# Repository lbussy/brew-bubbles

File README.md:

---
*It beats watching the grass grow!*

I just did a Google search:

That seems to be pretty important to many homebrewers. Nobody agrees what's "right," and about all the Internet can do is help you pass the time in between trips to stare at the airlock.

Wouldn't it be great if someone made something to tell you when your airlock is bubbling? At the very least, it would cut down on your significant other asking you where you are going at 2:00 AM as you tiptoe out of the bedroom by the light of your cellphone. I mean, we're in a day and age where you can ask your television questions. You'd think someone would make something that could help. What if you don't have computers connected to your grain bin and antennas on your growlers?

Enter Brew Bubbles.

Brew Bubbles will happily count every bubble and report it to you on a web page served by its own web server. Not enough? Brew Bubbles optionally allows you to hook in a couple of very inexpensive and standard temperature probes to display the fermenter and room temperature.

Still not enough, you say?

Well, if you want to go crazy, you can connect Brew Bubbles to [Brewer's Friend](https://www.brewersfriend.com/) and integrate the readings with your recipe journal and see how it all graphs out. Already wired at home? Connect Brew Bubbles into [BrewPi Remix](https://www.brewpiremix.com) or [Fermentrack](https://www.fermentrack.com) and amaze your friends!

Have I piqued your interest? Want to know how to get started? I'm glad you asked. The average garage handyman can build brew Bubbles for around $10, and it takes all of an hour before you are up and running.

Start with the [full documentation](https://brew-bubbles.readthedocs.io/en/latest/), or explore the repository here.

Brew Bubbles is a mature, stable product with no intended roadmap changes. It is maintained for historical reference only. No new releases, upgrades, or individual support are promised. Ask questions in [GitHub Discussions](https://github.com/lbussy/brew-bubbles/discussions) and report reproducible defects in [GitHub Issues](https://github.com/lbussy/brew-bubbles/issues). The original [HomeBrewTalk thread](https://homebrewtalk.com/threads/brew-bubbles-web-enabled-airlock.673559/) remains available as a historical community resource.

I really hope some of you will get some use out of this.

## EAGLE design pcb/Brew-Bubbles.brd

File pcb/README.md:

# 

# Brew Bubbles Shield

This folder contains the Eagle files for printed circuit boards supporting [Brew Bubbles](https://github.com/lbussy/brew-bubbles/).

The shield provides the necessary component connections and circuitry for the ESP-8266 controller used in this project.  It is nearly identical in size to the Wemos D1 mini we use to provide a very compact and lightweight footprint.

[Order from OSHPark.com](https://oshpark.com/shared_projects/NNPU5x7b):

- 2 layer board of 1.01 x 1.13 inches (25.6 x 28.7 mm) 
- $5.65 per set of 3

Please see [the documentation](https://brew-bubbles.readthedocs.io/en/latest/) for additional information.

## BOM

- 3 x C1 0.1μF Ceramic Capacitor (C1-3)
- *2 x 2.2kΩ 1/4W 5% Axial Resistors (R1-2)
- 1 x 150Ω 1/4W 5% Axial Resistor (R3)
- 1 x Sharp GP1A57HR Transmissive Photointerrupter (U1)
- *2 x 3-pin 90° Male Header (ROOM, VESSEL)

This section of the BOM is available on Mouser via [this link](https://www.mouser.com/ProjectManager/ProjectDetail.aspx?AccessID=216fcbe935).

Additionally you will need:

- 1 x Wemos D1 Mini (U2)
- 2 x 8-Pin stacking male headers (almost always comes with the D1)
- 2 x 8-Pin stacking female headers (almost always comes with the D1)
- *2 x Waterproof DS18B20 Temperature Sensor with lead

(*) - Optional items for use when temperature sensors are desired.  They are in the design to provide a means to monitor and trend one's ambient temperature where the fermenter is placed, and/or the fermenting liquid's temperature via a thermowell or insulated in contact with the fermenter. If one chooses not to use these, the firmware will automatically skip reporting these readings.

## 3D-Printed Bracket

See [this project on Thingiverse](https://www.thingiverse.com/thing:4020905) from @gromitdj on [Homebrewtalk.com](https://homebrewtalk.com) (original from @matridium on [Homebrewtalk.com](https://homebrewtalk.com)) for a bracket you can print.

## Modifying These Files
If you would like to personalize these board designs, you may modify them with [Autodesk has removed Eagle as a supported product, the PCBs have not been converted to KiCad].  

The program supports Windows, Linux, and Mac OS X.  EAGLE is available in a [free version](https://www.autodesk.com/products/eagle/free-download), as well as a [subscription-based version with more features](https://www.autodesk.com/products/eagle/compare).

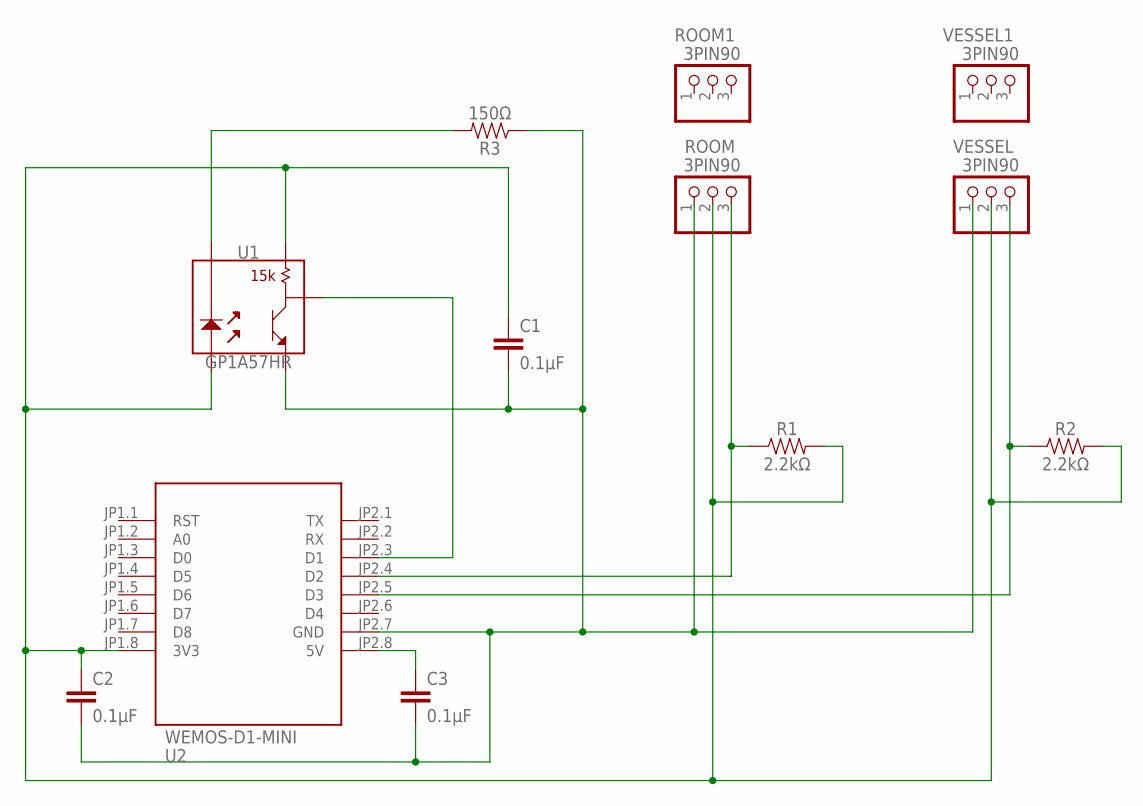
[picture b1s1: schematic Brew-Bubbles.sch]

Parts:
C1, C2, C3: 0.1μF; C025-024X044
R1, R2: 2.2kΩ; AXIAL-0.3
R3: 150Ω; AXIAL-0.3
ROOM, ROOM1: 3PIN90; 1X03/90
U1: GP1A57HR
U2: WEMOS-D1-MINI; WEMOS-D1-MINI-SHIELD
VESSEL, VESSEL1: 3PIN90; 1X03/90

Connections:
3V3: C1.1, C2.1, R1.P$2 (2), R2.P$2 (2), ROOM.2, U1.1, U1.3, U2.JP1.8 (3V3), VESSEL.2
5V: C3.1, U2.JP2.8 (5V)
D1: U1.4, U2.JP2.3 (D1)
D2: R1.P$1 (1), ROOM.3, U2.JP2.4 (D2)
D3: R2.P$1 (1), U2.JP2.5 (D3), VESSEL.3
GND: C1.2, C2.2, C3.2, R3.P$1 (1), ROOM.1, U1.5, U2.JP2.7 (GND), VESSEL.1
PD1: R3.P$2 (2), U1.2

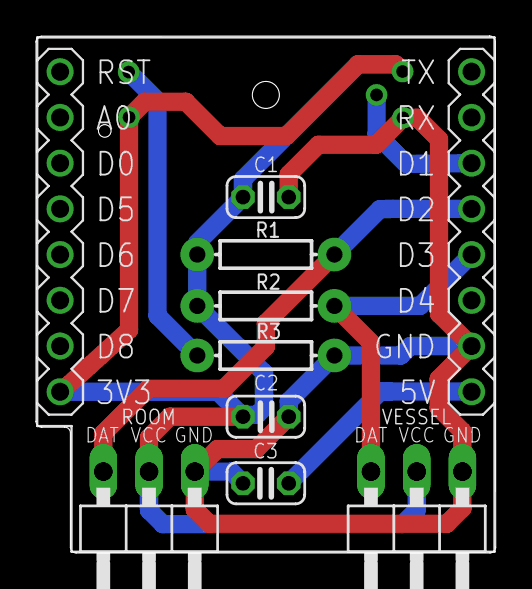
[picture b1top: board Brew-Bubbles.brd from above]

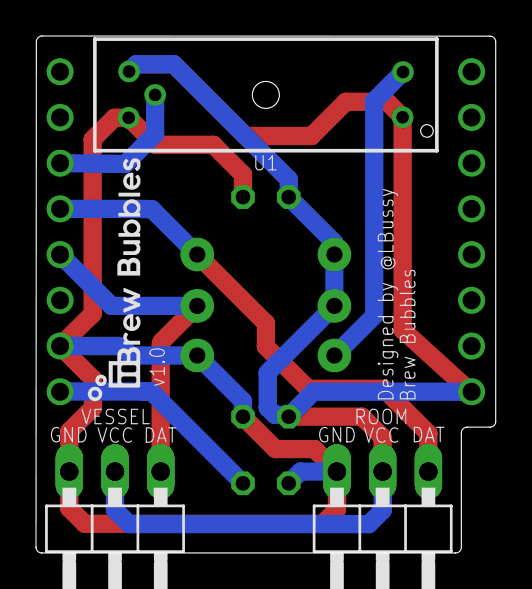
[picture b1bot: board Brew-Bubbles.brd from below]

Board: 2 copper layers, 25.5 x 28.7 mm, 12 parts (3 on the bottom side), 7 nets.

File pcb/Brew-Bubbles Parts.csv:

"Part";"Value";"Device";"Package";"Description";"POPULARITY";"PROD_ID";"SF_ID";"SPICEPREFIX";"VALUE";
"C1";"0.1μF";"C-EU025-024X044";"C025-024X044";"CAPACITOR, European symbol";"56";"";"";"C";"";
"C2";"0.1μF";"C-EU025-024X044";"C025-024X044";"CAPACITOR, European symbol";"56";"";"";"C";"";
"C3";"0.1μF";"C-EU025-024X044";"C025-024X044";"CAPACITOR, European symbol";"56";"";"";"C";"";
"R1";"2.2kΩ";"2K2OHM-HORIZ-1/4W-5%";"AXIAL-0.3";"2K2Ω resistor";"";"RES-8371";"";"";"2200";
"R2";"2.2kΩ";"2K2OHM-HORIZ-1/4W-5%";"AXIAL-0.3";"2K2Ω resistor";"";"RES-8371";"";"";"2200";
"R3";"150Ω";"150OHM-HORIZ-1/4W-5%";"AXIAL-0.3";"150Ω resistor";"";"RES-8371";"";"";"150";
"ROOM";"3PIN90";"PINHD-1X3/90";"1X03/90";"PIN HEADER";"17";"";"";"";"";
"U1";"GP1A57HR";"GP1A57HR";"GP1A57HR";"Sharp GP1A57HR Transmissive Photointerrupter";"";"";"SEN-09299";"";"";
"U2";"WEMOS-D1-MINI";"WEMOS-D1-MINI";"WEMOS-D1-MINI";"WEMOS D1 mini";"";"";"";"";"";
"VESSEL";"3PIN90";"PINHD-1X3/90";"1X03/90";"PIN HEADER";"17";"";"";"";"";

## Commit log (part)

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2020-04-17 Move to controlled repos
2020-04-17 Change filenames
2020-04-17 Allow clearing keys/urls
2020-04-17 Update TODO
2020-04-17 Enable posting to Brewfather
2020-04-17 Rename files
2020-04-17 Correctly determine posting status
2020-04-17 Remove '?' in querystring when posting
2020-04-18 Add reset handling
2020-04-18 Add delay before restart()
2020-04-18 Reset page now reloads gracefully
2020-04-18 Rename 'restart' to 'reset'
2020-04-18 Cleanup reset logic
2020-04-18 Debug output formatting
2020-04-18 Address crashing on resets (#19)
2020-04-18 Remove debug
2020-04-18 Update docs for BrewFlasher
2020-04-18 No longer used
2020-04-18 RC version of firmware
2020-04-18 Compile version 2.0.0
2020-04-18 Compile version 2.0.0 (replace damaged files)
2020-04-20 Add query type
2020-04-20 Add Thingspeak handler
2020-04-20 Formatting change only
2020-05-19 Bracket with collimator added
2020-07-25 #25 Add LittleFS support
2020-07-26 #24 switch Brewfather ext_temp to aux_temp (room)
2020-07-26 Cleanup LittleFS stuff
2020-07-26 Update devel firmware
2020-07-26 Update for LittleFS
2020-07-26 Typo
2020-07-29 No longer using firmware tools
2020-07-29 Remove some debug notes
2020-07-29 Update 2.1.0 firmware
2020-07-29 Fix version
2020-07-29 Move ticker loop to tools. Move ota to loop
2020-07-29 Added debug line (commented)
2020-07-29 firmware
2020-08-04 Update additional spiffs to littlefs references
2020-08-04 Remove debug print
2020-08-04 Update firmware version
2020-08-04 Actually updated the version this time
2020-08-12 CHange to white BG on web portal
2020-08-12 Format source files
2020-08-12 Move loop processing to push helper
2020-08-12 Update to use LCBUrl for IP
2020-08-12 Add reference model
2020-08-13 Initial work for ThingSpeak
2020-08-13 Add updated firmware
2020-08-13 Wipe array on format change
2020-09-08 Add Brew Bubbles mDNS service
2020-11-20 Add /uptime/ json report
2020-11-20 Add /resetreason/ json report
2020-11-20 Improve /heap/ json report
2020-11-20 Move reports to json handler section
2020-11-20 Remove TODO
2020-11-20 Stub in debug querys
2020-11-21 Remove Thingspeak for now
2020-11-21 Add a working mdns reset
2020-11-21 Address wifi connect issues
2020-11-21 Cleanup logic
2020-11-21 Bring in common wifi handling
2020-11-21 Add maintenance loop
2020-11-21 Fix mdns hostname
2020-11-21 Start bringing in Telnet
2020-11-21 Fix ntp hack
2020-11-21 Add uptime work
2020-11-21 --amend
2020-11-21 Add telnet handler
2020-11-21 Save BPM at each tick
2020-11-21 Update page headings
2020-11-22 Add debug information
2020-11-22 Update firmware
2020-11-28 Formatting and spelling
2020-11-28 Update version
2020-11-28 Update docs for LittleFS
2020-11-28 Add debug and update page header
2020-11-28 Update wifi handler
2020-11-28 Spelling
2020-11-28 Update serial handling
2020-11-28 Add mdnsreset handling
2020-11-28 Add uptime reporting
2020-11-28 Add Gerber files
2020-11-28 Add telnet
2020-11-28 Save BPM on each tick
2020-11-28 Allow non-blocking reconnect
2020-11-28 Shorten ota flow
2020-11-28 Add ThingSpeak configuration
2020-11-28 More ThingSpeak backend support
2020-11-28 Add in timer support for TS
2020-11-28 Commit ThingSpeak posting
2020-11-28 Remove lockup with no time hack
2020-11-28 Add tooltip to web page debug
2020-11-28 Update to ThingSpeak release alpha
2020-11-29 Fix ThingSpeak timer
2020-11-29 Lower heap threshold
2020-11-29 Remove reload on submit
2020-11-29 Disable ThingSpeak on no key/channel
2020-11-29 2.2.0RC1
2020-12-02 Address NaN bubbles after flash
2020-12-02 Improve lastBpm capabilities
2020-12-02 Fix issue with no config json found
2020-12-02 Center copyright notice
2020-12-02 Fix formatting of debug message
2020-12-02 Don't save lastBpm when rebooting out of AP
2020-12-02 Set to debug mode
2020-12-03 Add About page reload, branch and commit
2020-12-03 Fixed error in wrong span
2020-12-03 Use new DRD, fix DRD on flash
2020-12-03 Fix form boundary
2020-12-03 Add TOC to pages needing it
2020-12-03 Update the API pages
2020-12-03 Change all PCB links to OSH Park
2020-12-03 Prepare 2.2.0RC2
2020-12-04 Improve uptime calculations
2020-12-04 Fix rollover issue, simplify
2020-12-05 Make webpage report 'Not connected' on disco sensors
2020-12-06 Make disconnected sensors work properly #23
2020-12-06 Prep RC3
2020-12-06 Add CT's bubbles back to debug
2020-12-06 Add writeup about pinhole cameras
2020-12-06 Add 2.2.0 firmware
2020-12-06 Update firmware for 2.2.0 Devel
2020-12-06 --apend
2020-12-06 Release 2.2.0
2020-12-06 Reduce DRD time to 3 secs
2020-12-09 Add link to GitHub discussions
2021-01-03 Fix preprocessor macros from ESP32
2021-01-03 Put version in platformio.ini
2021-01-03 Update firmware package
2021-02-13 Add nodrd flag to config
2021-02-13 Update bug release version
2021-02-13 Move to LWIP v1.4 High
2021-02-13 Bugfix Release 2.2.2 (#42)
2021-02-13 Add 2.2.2 firmware
2021-02-14 Adjust debug
2021-02-20 Couple changes for a Mac
2021-02-20 Fix month (was 0 index)
2021-02-20 Add timezone support
2021-02-20 Update copyright date
2021-02-20 Allow disabling editor:
2021-02-20 Remove some debug
2021-02-20 Remove editor
2021-02-20 Print millis() before time hack is received
2021-02-20 Get rid of uneeded code
2021-02-20 Return to upstream
2021-02-20 Remove unused variable
2021-02-20 Remove redeclarations
2021-02-20 Add Day of Week
2021-02-21 Set proper timezone
2021-02-21 Add warking about lwIP
2021-02-21 Add ntp configuration for lwIP 1.x
2021-02-21 Promote 2.2.3beta for #43
2021-02-21 Fix NTP with lwIP 1.4 (#44)
    * Fix month (was 0 index)
    * Add timezone support
    * Update copyright date
    * Allow disabling editor:
    * Remove some debug
    * Remove editor
2021-02-21 Promote to 2.2.3 devel
2021-02-21 Move back to private repo
2021-02-21 Add master 2.2.3
2021-06-09 Update docs with metal tape collimator
2021-06-09 Fix typos
2021-06-10 Reinstate TZ
2021-06-10 Support long longs in ArduinoJson
2021-06-10 Speed uploads
2021-06-10 Remove deprecated declaration
2021-06-10 Remove millis from uptime
2021-06-10 Remove potential buffer overflow
2021-06-10 Use updated lib
2021-06-10 Remove unused method
2021-06-11 Get rid of issue with const
2021-06-11 Framework update (#48)
    * f719340 Reinstate TZ
    * 8a46629 Support long longs in ArduinoJson
    * f39229d Speed uploads
    * cda685f Remove deprecated declaration
    * 3316a14 Remove millis from uptime
    * 6926790 Remove potential buffer overflow
2021-06-11 Change environment
2021-06-11 New scripts
2021-06-11 Add FS version
2021-06-11 Modify for project
2021-06-12 Use new firmware names
2021-06-12 Add beta flag and reset on failed connect
2021-06-12 New file
2021-06-12 Updated firmware
2021-06-12 Fix link
2021-06-12 Allow switching to beta
2021-06-12 Remove whitespace
2021-06-12 Remove old src tag
2023-03-02 Moving to MyST
2023-08-19 Use main on LCBUrl
2023-08-19 Remove firmware
2023-08-19 Merge Old Devel (#54)
    * Update docs with metal tape collimator
    * Framework update (#48)
    * f719340 Reinstate TZ
    * 8a46629 Support long longs in ArduinoJson
    * f39229d Speed uploads
    * cda685f Remove deprecated declaration
2023-08-19 Initial conversion to MyST
2023-08-19 Initial conversion to MyST (#55)
2023-08-19 Remove (some) priv libs
2023-08-19 Remove (some) priv libs (#56)
2023-08-19 Move includes
2023-08-19 Move includes (#57)
2023-08-20 Remove errs in libs
2023-08-20 Remove errs in libs (#58)
2023-08-20 Add readthedocs.yaml
2023-08-20 Fix tags
2023-08-20 Try v3.10
2023-08-20 Fix Py ver
2023-08-21 Re-do without Async
2023-08-22 Add fs edit
2023-08-25 Get off shitty async
2023-08-25 Fix CR/LF
2023-08-25 Size JSON
2023-08-27 Reuse FS Object
2023-08-27 Revamp tools
2023-08-27 Update Copyright
2023-08-27 Put config save in loop
2023-08-27 Use current WiFiManager
2023-08-27 Remove Async (#59)
    * Re-do without Async
    * Add fs edit
    * Fix CR/LF
    * Size JSON
    * Reuse FS Object
    * Revamp tools
2025-03-27 Add rtd yaml
2025-03-27 Add rtd yaml (#62)
2025-03-27 Fix documentation (for now)

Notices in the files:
parts and their libraries:
diy-modules: Released under the Creative Commons Attribution 4.0 International License: http://creativecommons.org/licenses/by/4.0
SparkFun-Sensors: Licensing: Creative Commons ShareAlike 4.0 International - https://creativecommons.org/licenses/by-sa/4.0
